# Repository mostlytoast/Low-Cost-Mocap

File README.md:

# Low Cost Mocap For all!

### An extention to a cheap open source motion capture system with improved tools and cameras

## Goal of project

This project was started to take an existing motion capture system made by [jyjblrd](https://github.com/jyjblrd/Low-Cost-Mocap) and improve it so it can become an easy to use and accessible system. Thus providing a low cost alternative for motion capture systems costing only a few hundred dollars, which is significantly cheaper to current multi thousand dollar commercial systems. The main use case for this system is at smaller schools and hobbyists that need motion tracking systems for robotics and research applications.
To achieve this many improvements were made to hardware and software which are detailed bellow.

## Cameras

In previous iterations of this system PlayStation Eye cameras were used which required heavy modifications. This is no longer the case with a new and improved 3d printed case for the Arducam OV9281 usb webcam.

## Camera calibration

Another improvement is a dedicated app for camera calibration which provides intuitive steps for how to setup a system, shown bellow.

On the left users add cameras they wish to use for their setup to the "added webcams" list using arrows or keyboard shortcuts. They can also select webcams and view a preview by clicking "Open Camera". Additionally settings can be edited and have an instant preview of their effects in the preview window. To the right is the camera calibration page where users can use a predetermined checkerboard to calibrate each camera. Once all cameras are calibrated the user can save the current configuration and use it with the tracking application.

## Tracking app

The previous JS GUI implementation was replaced with an improved more portable PyQt application. This reduced dependencies making the application more portable and have a smaller file size, as well as being more performant.

The application provides the user with a clutter free experience showing them only what they need to get the system working. This includes camera Controls for exposure and gain as well as calibration and setup options. Once a system has been calibrated the configuration can be saved to be used again.

## Dependencies

The only dependency required is Python 3.12. and has only been tested to be fully working on linux. Full support for Windows and MacOS remains unimplemented as the videoSubsystem needs to be modified to support it, and platforms like MacOS limit control for usb cameras meaning exposure can not be set for cameras.

## Running the code

In the project directory run the install script with make and then open python virtual environment if it does not automatically do so.

```
$ make install 
$ source venv/bin/activate
```

Then run either the calibration or tracking app by running `make calib` or `make tracking` respectively.

## Compile to binaryne of the main reasons for removing JavaScript from this project was so PyInstaller could be used to create a portable executable making the project more accessible to normal users. Currently the binary has to be compiled manually which can be done by running `make compileCalib` and then `make compileTracking` to generate the exe for each. The executable for each can be found in computer_code/api/dist and can be run using commands `make calibEXE` and then `make trackingEXE`.

    Currently work is being done to combine both of these programs into one application which would reduce file sizes for the installer.

## Other repositories used

For 3d viewport in the tracking application I used the [PyQt5 Mesh Viewer](https://github.com/zishun/pyqt-meshviewer) by [zishun](https://github.com/zishun/pyqt-meshviewer/commits?author=zishun) with some extra modifications to support more features like zoom, displaying grids, etc.

## Useful tools

if you plan on working on the UI for this project consider using [ PyQtInspect](https://github.com/JezaChen/PyQtInspect-Open) which is a very useful tool to debug potential layout bugs.

`./computer_code/venv/bin/python3  -m PyQtInspect --direct --multiprocess --show-pqi-stack --qt-support=pyqt5 --file computer_code/api/cameraCalibGcomputer_code.Ui.py `

## Pushing releases

releases are compiled by pushing to the main branch with a version tag greater then currently released version. It will be automatically packaged and shown on the releases tab when the push is accepted.

## Documentation

The documentation for this project is admittedly pretty lacking, if anyone would like to put type definitions in the Python code that would be amazing and probably go a long way to helping the readability of the code. Feel free to also use the [discussion](https://github.com/jyjblrd/Mocap-Drones/discussions) tab to ask questions.

My blog post has some more information about the drones & camera: [joshuabird.com/blog/post/mocap-drones](https://joshuabird.com/blog/post/mocap-drones)

## YouTube Video

Watch this for information about the project & a demo!
[https://youtu.be/0ql20JKrscQ?si=jkxyOe-iCG7fa5th](https://youtu.be/0ql20JKrscQ?si=jkxyOe-iCG7fa5th)

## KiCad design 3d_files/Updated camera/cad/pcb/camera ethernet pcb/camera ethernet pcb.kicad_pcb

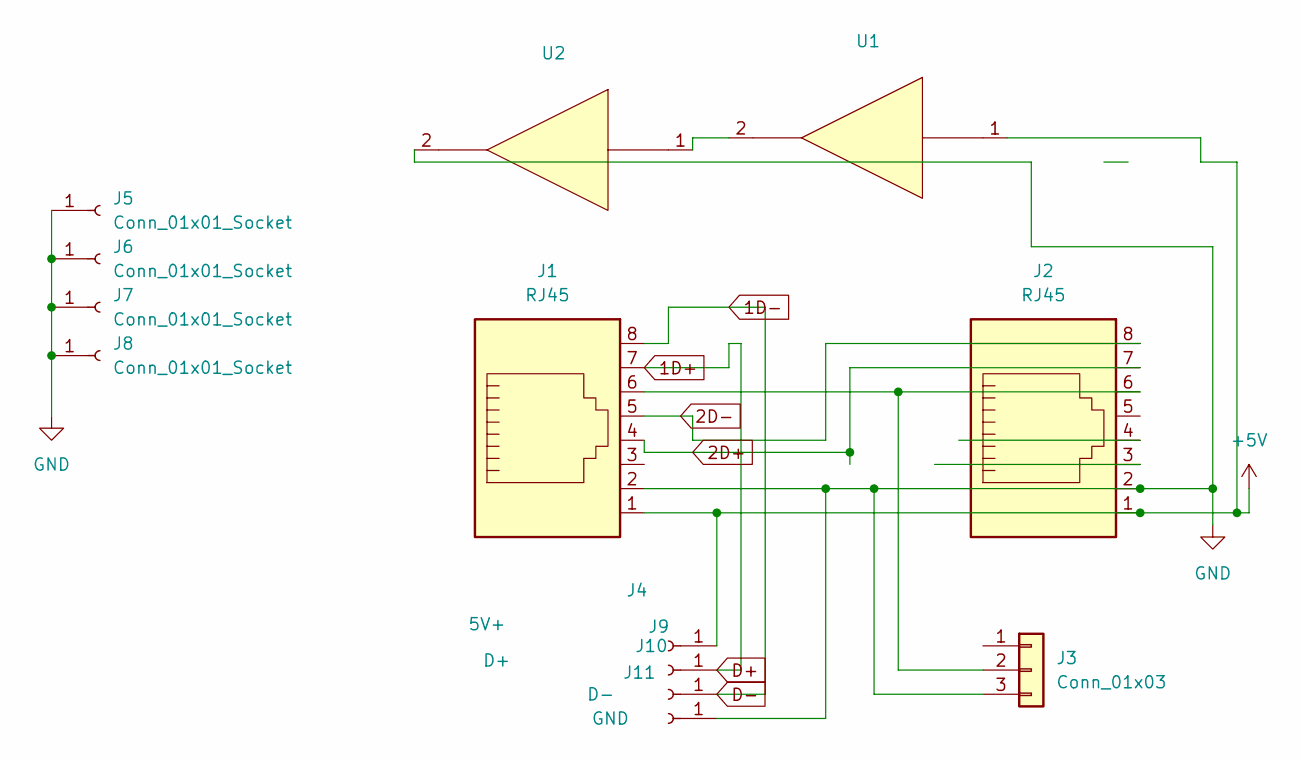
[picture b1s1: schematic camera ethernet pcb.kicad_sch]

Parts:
J1, J2: RJ45
J3: Conn_01x03; PinHeader_1x03_P1.00mm_Vertical
J4: 5V+; TestPoint_THTPad_1.0x1.0mm_Drill0.5mm
J5, J6, J7, J8: Conn_01x01_Socket; MountingHole_2.2mm_M2_ISO7380_Pad
J9: D+; TestPoint_THTPad_1.0x1.0mm_Drill0.5mm
J10: D-; TestPoint_THTPad_1.0x1.0mm_Drill0.5mm
J11: GND; TestPoint_THTPad_1.0x1.0mm_Drill0.5mm
U1, U2: IR_LED

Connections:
1D+: J1.7, J9.1
1D-: J1.8, J10.1
2D+: J1.4, J2.7
2D-: J1.5, J2.8
+5V: J1.1, J2.1, J4.1, U1.1
GND: J1.2, J2.2, J3.3, J5.1, J6.1, J7.1, J8.1, J11.1, U2.2
unnamed: J1.6, J2.6, J3.2
unnamed: U1.2, U2.1

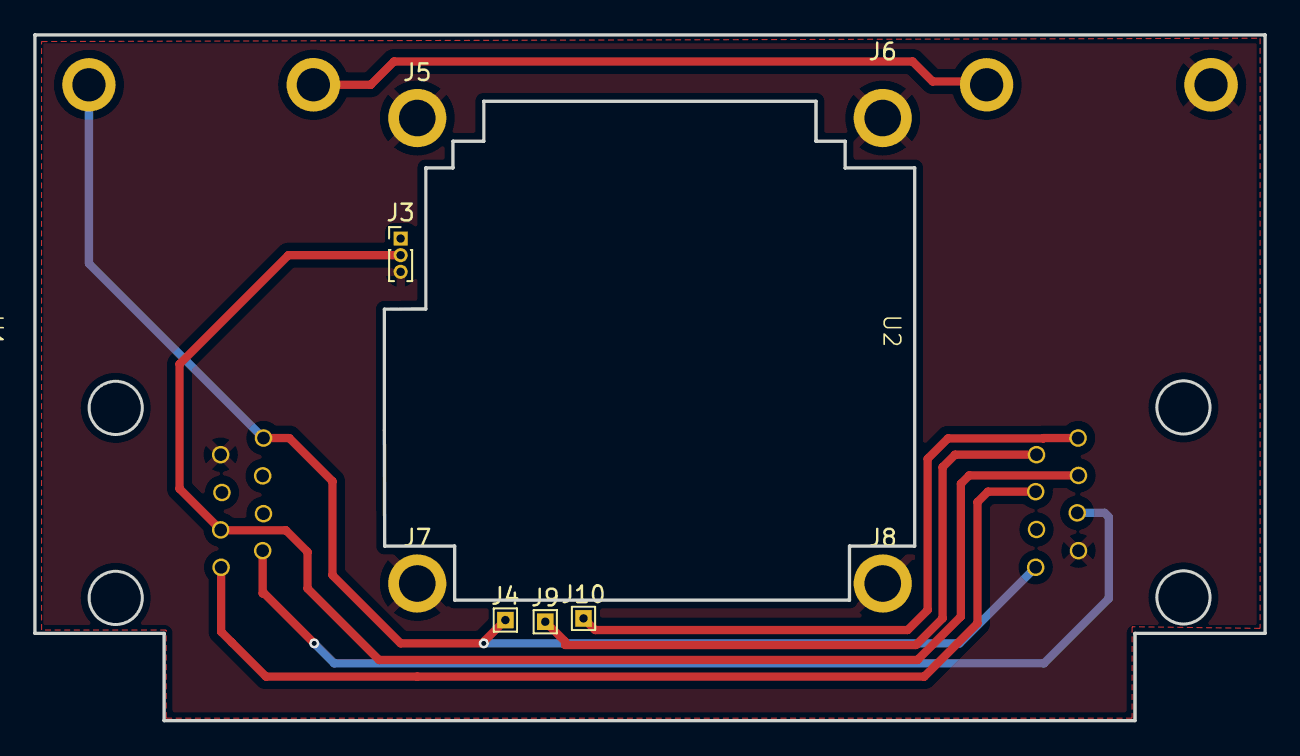
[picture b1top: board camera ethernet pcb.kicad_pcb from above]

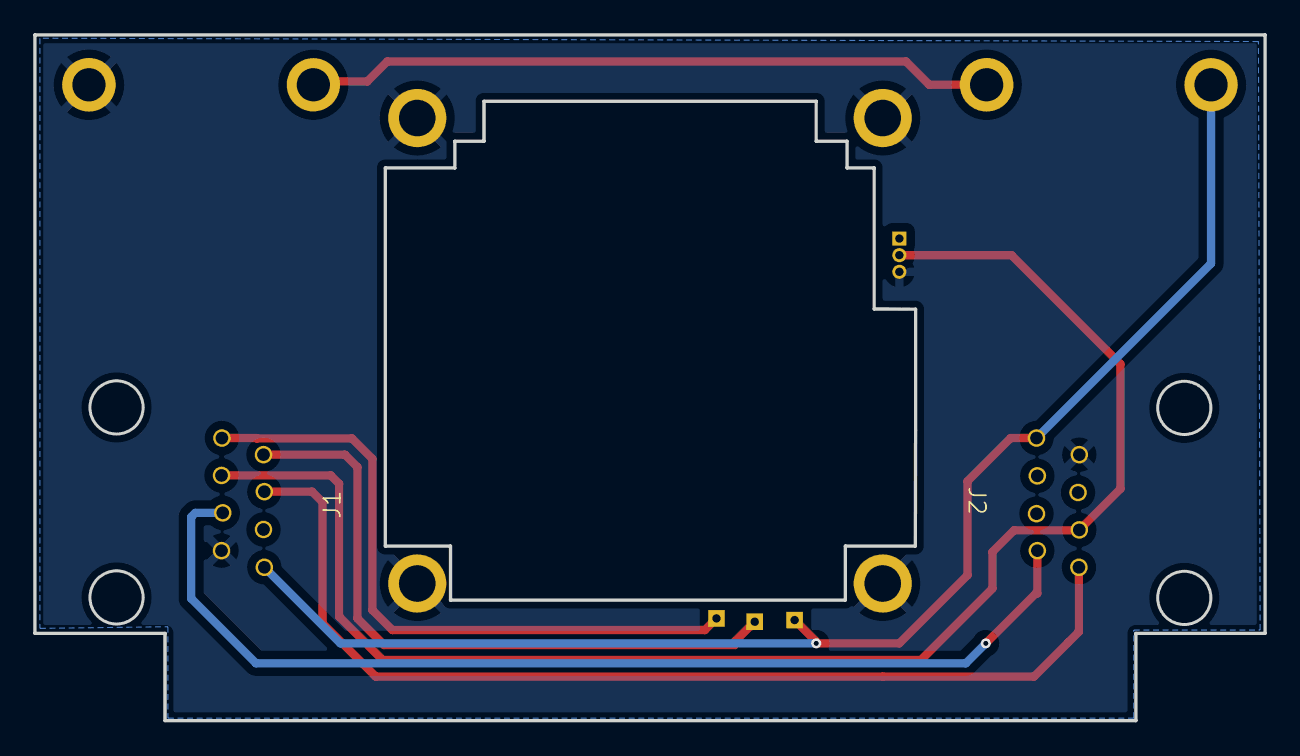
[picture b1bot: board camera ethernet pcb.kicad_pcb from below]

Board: 2 copper layers, 74.0 x 41.2 mm, 12 parts (2 on the bottom side), 8 nets.

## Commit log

2024-08-20 enable generic usb webcams disabled serial added unfinished camera calibration setup
2024-08-20 no drone normal webcams
2024-08-31 added test files, better camera handling todo fix acquire_floor
2025-05-21 update documentation
2025-05-21 fixes to acquire floor
2025-05-25 included cad files for new camera design
2025-05-26 random fixes added todo list
2025-06-03 improved camera setup
2025-06-03 calib images saved in memory, save settings to json
2025-06-03 fix start for config
2025-06-04 added tests and minor refactor
2025-06-04 updates to cmd interface and improved tests
2025-06-04 add profiler
2025-06-04 temp
2025-06-10 try adding tests
2025-06-10 fixed tests and installer
2025-06-10 removed profiler files
2025-06-11 updates to installer tinker with acquire floor
2025-06-18 add more documentation and PyQt
2025-06-19 add gui for camera calibration
2025-06-19 compiled to exe
2025-06-19 initial gui camera selection working
2025-06-19 testing editing
2025-06-19 refactor to have separate classes for different layouts
2025-06-22 improve gui
2025-06-22 attempt to reduce size
2025-06-22 add style
2025-06-23 attempt floor fix
2025-06-23 add install file
2025-06-23 images
2025-06-24 mostly working app
2025-06-24 added 3d viewer
2025-06-24 added live triangulation with minor bugs
2025-06-24 untested open
2025-06-24 small fixes
2025-06-24 attempt to fix fps
2025-06-24 ui improvements
2025-06-24 removed files
2025-06-24 implemented gui need to bug test set scale and fix floor
2025-06-24 attempt to fix sfm and other floor bugs
2025-06-25 add resolution change
2025-06-25 before refactor
2025-06-25 undo refactor
2025-06-25 added checks for exposure info
2025-06-25 refactor and used camera singleton as data structure
2025-06-26 refactoring
2025-06-26 add diagram file
2025-06-26 clean up
2025-06-26 add more calib features
2025-06-26 minor changes
2025-06-27 working partial refactor
2025-06-27 more refactoring and added test cases for ui
2025-06-28 add images for test
2025-06-28 test cases clean up before settings refactor
2025-06-28 test adding app to cameraCalibGui
2025-06-28 fix to combined implementation
2025-07-03 add images
2025-07-03 add videos minor changes
2025-07-03 replace vid with gif
2025-07-03 update read me
2025-07-03 floor is working need to fix save function
2025-07-03 working floor and save (is upside down)
2025-07-03 fix camera calib
2025-07-04 added label refresh button
2025-07-04 remove files
2025-07-04 move files around
2025-07-04 freeze linux info on line 124 of eventrecord.py
2025-07-04 attempt to make event recorder
2025-07-04 removed dir
2025-07-16 add error checking for index calculate camera pose
2025-07-16 add some error checking
2025-07-16 refactor
2026-02-18 Update project title for clarity
2026-04-06 attempt to get working deployment
2026-04-06 Add GitHub Actions workflow for Python deployment
2026-04-06 set shell to bash
2026-04-06 add debug info to make file
2026-04-06 update to make and install
2026-04-06 added missing dependencies
2026-04-06 attempt to fix pyinstaller issue
2026-04-06 update yml
2026-04-06 fix makefile issues and force tag for version
2026-04-07 update pyinstaller for missing packages
2026-04-07 fix stuff
2026-04-07 remove extra compile
2026-04-07 update make file again
2026-04-07 fix makefile
2026-04-07 fix string
2026-04-07 reformat and add tracking app for compile
2026-04-07 fix workflow
2026-04-07 attempt to build for mac and windows
2026-04-07 undo build changes
2026-04-07 working macos view app
2026-04-12 add some support for macos and refactor
2026-04-12 more refactoring and working tests
2026-04-14 fixes and docs
2026-04-15 work on new thread structure
2026-04-15 attempt to get speedup having issues with multiple cameras unsure
